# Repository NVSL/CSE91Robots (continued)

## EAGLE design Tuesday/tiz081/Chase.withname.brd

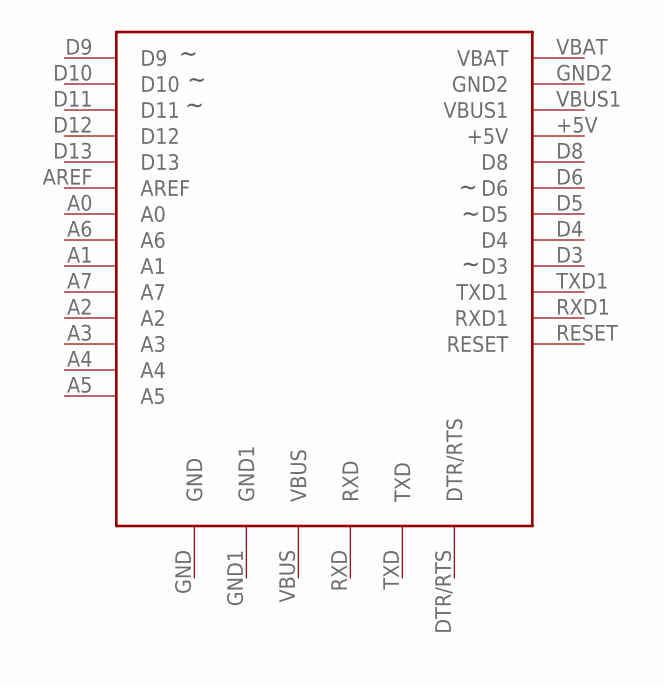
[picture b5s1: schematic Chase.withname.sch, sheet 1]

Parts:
U1_0_BRAIN: ADAFRUIT-PRO-TRINKET-5V-BOB; ADAFRUIT-PRO-TRINKET-5V

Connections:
+5V_0_BRAIN: U1_0_BRAIN.+5V; also elsewhere on the board
A0_0_BRAIN: U1_0_BRAIN.A0; also elsewhere on the board
A1_0_BRAIN: U1_0_BRAIN.A1; also elsewhere on the board
A2_0_BRAIN: U1_0_BRAIN.A2; also elsewhere on the board
A3_0_BRAIN: U1_0_BRAIN.A3; also elsewhere on the board
A4_0_BRAIN: U1_0_BRAIN.A4
A5_0_BRAIN: U1_0_BRAIN.A5
A6_0_BRAIN: U1_0_BRAIN.A6
A7_0_BRAIN: U1_0_BRAIN.A7
AREF_0_BRAIN: U1_0_BRAIN.AREF
D3_0_BRAIN: U1_0_BRAIN.D3; also elsewhere on the board
D4_0_BRAIN: U1_0_BRAIN.D4; also elsewhere on the board
D5_0_BRAIN: U1_0_BRAIN.D5; also elsewhere on the board
D6_0_BRAIN: U1_0_BRAIN.D6; also elsewhere on the board
D8_0_BRAIN: U1_0_BRAIN.D8; also elsewhere on the board
D9_0_BRAIN: U1_0_BRAIN.D9; also elsewhere on the board
D10_0_BRAIN: U1_0_BRAIN.D10; also elsewhere on the board
D11_0_BRAIN: U1_0_BRAIN.D11; also elsewhere on the board
D12_0_BRAIN: U1_0_BRAIN.D12; also elsewhere on the board
D13_0_BRAIN: U1_0_BRAIN.D13; also elsewhere on the board
DTR/RTS_0_BRAIN: U1_0_BRAIN.DTR/RTS
GND2_0_BRAIN: U1_0_BRAIN.GND, U1_0_BRAIN.GND1, U1_0_BRAIN.GND2; also elsewhere on the board
RESET_0_BRAIN: U1_0_BRAIN.RESET
RXD1_0_BRAIN: U1_0_BRAIN.RXD1
RXD_0_BRAIN: U1_0_BRAIN.RXD
TXD1_0_BRAIN: U1_0_BRAIN.TXD1
TXD_0_BRAIN: U1_0_BRAIN.TXD
VBUS1_0_BRAIN: U1_0_BRAIN.VBUS1
VBUS_0_BRAIN: U1_0_BRAIN.VBUS
VM_2_DRIVE: U1_0_BRAIN.VBAT; also elsewhere on the board

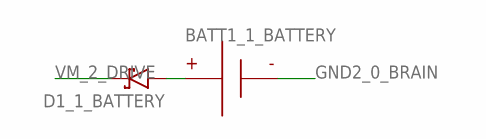
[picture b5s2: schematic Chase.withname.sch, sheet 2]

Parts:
BATT1_1_BATTERY: BATTERY-9V-VERTICAL; BATTERY_9V_KEYSTONE_968
D1_1_BATTERY: RESOLVED-DIODE-SCHOTTKY_TH-DO-41-AND-DO-204AL; DIOAD1125W78L520D270_HS; MPN 1N5817

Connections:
GND2_0_BRAIN: BATT1_1_BATTERY.N; also elsewhere on the board
unnamed: BATT1_1_BATTERY.P, D1_1_BATTERY.A
VM_2_DRIVE: D1_1_BATTERY.C; also elsewhere on the board

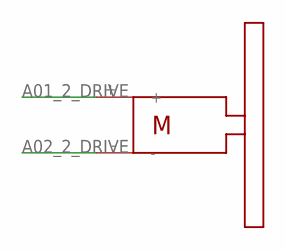
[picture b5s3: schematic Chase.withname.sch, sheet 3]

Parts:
R_2_DRIVE: SOLARBOTICS_GM2SPARKFUN_HOBBY; SPARKFUN_HOBBY_MOTOR

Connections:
A01_2_DRIVE: R_2_DRIVE.+; also elsewhere on the board
A02_2_DRIVE: R_2_DRIVE.-; also elsewhere on the board

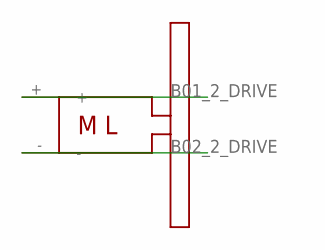
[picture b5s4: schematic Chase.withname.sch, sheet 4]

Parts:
L_2_DRIVE: SOLARBOTICS_GM2_LEFTSPARKFUN_HOBBY; SPARKFUN_HOBBY_MOTOR_LEFT

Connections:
B01_2_DRIVE: L_2_DRIVE.+; also elsewhere on the board
B02_2_DRIVE: L_2_DRIVE.-; also elsewhere on the board

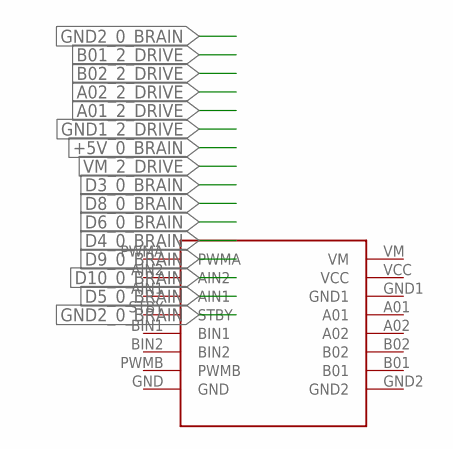
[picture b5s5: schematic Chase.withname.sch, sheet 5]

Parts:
DRVR_2_DRIVE: SPARKFUN_DUAL_MOTOR_DRIVER-BOB; SPARKFUN_DUAL_MOTOR_DRIVER

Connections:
+5V_0_BRAIN: DRVR_2_DRIVE.VCC; also elsewhere on the board
A01_2_DRIVE: DRVR_2_DRIVE.A01; also elsewhere on the board
A02_2_DRIVE: DRVR_2_DRIVE.A02; also elsewhere on the board
B01_2_DRIVE: DRVR_2_DRIVE.B01; also elsewhere on the board
B02_2_DRIVE: DRVR_2_DRIVE.B02; also elsewhere on the board
D3_0_BRAIN: DRVR_2_DRIVE.PWMA; also elsewhere on the board
D4_0_BRAIN: DRVR_2_DRIVE.STBY; also elsewhere on the board
D5_0_BRAIN: DRVR_2_DRIVE.PWMB; also elsewhere on the board
D6_0_BRAIN: DRVR_2_DRIVE.AIN1; also elsewhere on the board
D8_0_BRAIN: DRVR_2_DRIVE.AIN2; also elsewhere on the board
D9_0_BRAIN: DRVR_2_DRIVE.BIN1; also elsewhere on the board
D10_0_BRAIN: DRVR_2_DRIVE.BIN2; also elsewhere on the board
GND1_2_DRIVE: DRVR_2_DRIVE.GND1
GND2_0_BRAIN: DRVR_2_DRIVE.GND, DRVR_2_DRIVE.GND2; also elsewhere on the board
VM_2_DRIVE: DRVR_2_DRIVE.VM; also elsewhere on the board

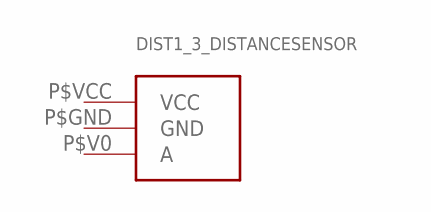
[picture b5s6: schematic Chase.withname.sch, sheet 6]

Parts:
DIST1_3_DISTANCESENSOR: ANALOG_DISTANCE_SENSOR

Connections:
+5V_0_BRAIN: DIST1_3_DISTANCESENSOR.P$VCC (VCC); also elsewhere on the board
A2_0_BRAIN: DIST1_3_DISTANCESENSOR.P$V0 (A); also elsewhere on the board
GND2_0_BRAIN: DIST1_3_DISTANCESENSOR.P$GND (GND); also elsewhere on the board

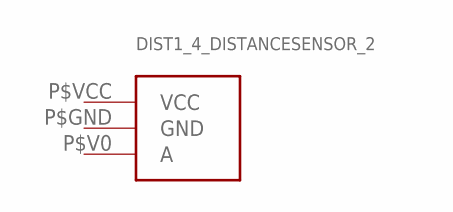
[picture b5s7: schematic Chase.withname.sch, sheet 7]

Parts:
DIST1_4_DISTANCESENSOR_2: ANALOG_DISTANCE_SENSOR

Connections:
+5V_0_BRAIN: DIST1_4_DISTANCESENSOR_2.P$VCC (VCC); also elsewhere on the board
A3_0_BRAIN: DIST1_4_DISTANCESENSOR_2.P$V0 (A); also elsewhere on the board
GND2_0_BRAIN: DIST1_4_DISTANCESENSOR_2.P$GND (GND); also elsewhere on the board

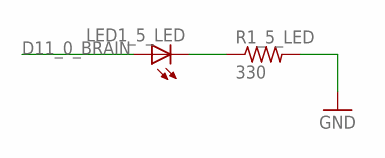
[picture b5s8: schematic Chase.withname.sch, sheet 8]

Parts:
LED1_5_LED: LED5MM
R1_5_LED: 330; RESAD770W45L370D210_HS; MPN CFR-12JB-52-330R

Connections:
D11_0_BRAIN: LED1_5_LED.A; also elsewhere on the board
GND2_0_BRAIN: R1_5_LED.2; also elsewhere on the board
unnamed: LED1_5_LED.K (C), R1_5_LED.1

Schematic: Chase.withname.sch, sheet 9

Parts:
LED1_6_LED_2: LED5MM
R1_6_LED_2: 330; RESAD770W45L370D210_HS; MPN CFR-12JB-52-330R

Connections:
D12_0_BRAIN: LED1_6_LED_2.A; also elsewhere on the board
GND2_0_BRAIN: R1_6_LED_2.2; also elsewhere on the board
unnamed: LED1_6_LED_2.K (C), R1_6_LED_2.1

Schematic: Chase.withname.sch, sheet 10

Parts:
LED1_7_LED_3: LED5MM
R1_7_LED_3: 330; RESAD770W45L370D210_HS; MPN CFR-12JB-52-330R

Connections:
D13_0_BRAIN: LED1_7_LED_3.A; also elsewhere on the board
GND2_0_BRAIN: R1_7_LED_3.2; also elsewhere on the board
unnamed: LED1_7_LED_3.K (C), R1_7_LED_3.1

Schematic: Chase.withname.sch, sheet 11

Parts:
U1_8_CASTER: CASTERADAFRUIT-3/4IN; ADAFRUIT-3/4IN-CASTER

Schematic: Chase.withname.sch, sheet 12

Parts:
B1_9_BUTTON: BUTTON-TACTILE-ROUND; BUTTON-TACTILE-ROUND-ADAFRUIT1009

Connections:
A0_0_BRAIN: B1_9_BUTTON.P; also elsewhere on the board
GND2_0_BRAIN: B1_9_BUTTON.S; also elsewhere on the board

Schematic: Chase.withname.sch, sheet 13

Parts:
U$2_10_BUMP: BUMP_SWITCH-MEDIUM-RIGHT; BUMP_SWITCH_OMRON_D2FLA1

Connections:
A1_0_BRAIN: U$2_10_BUMP.A; also elsewhere on the board
GND2_0_BRAIN: U$2_10_BUMP.B; also elsewhere on the board

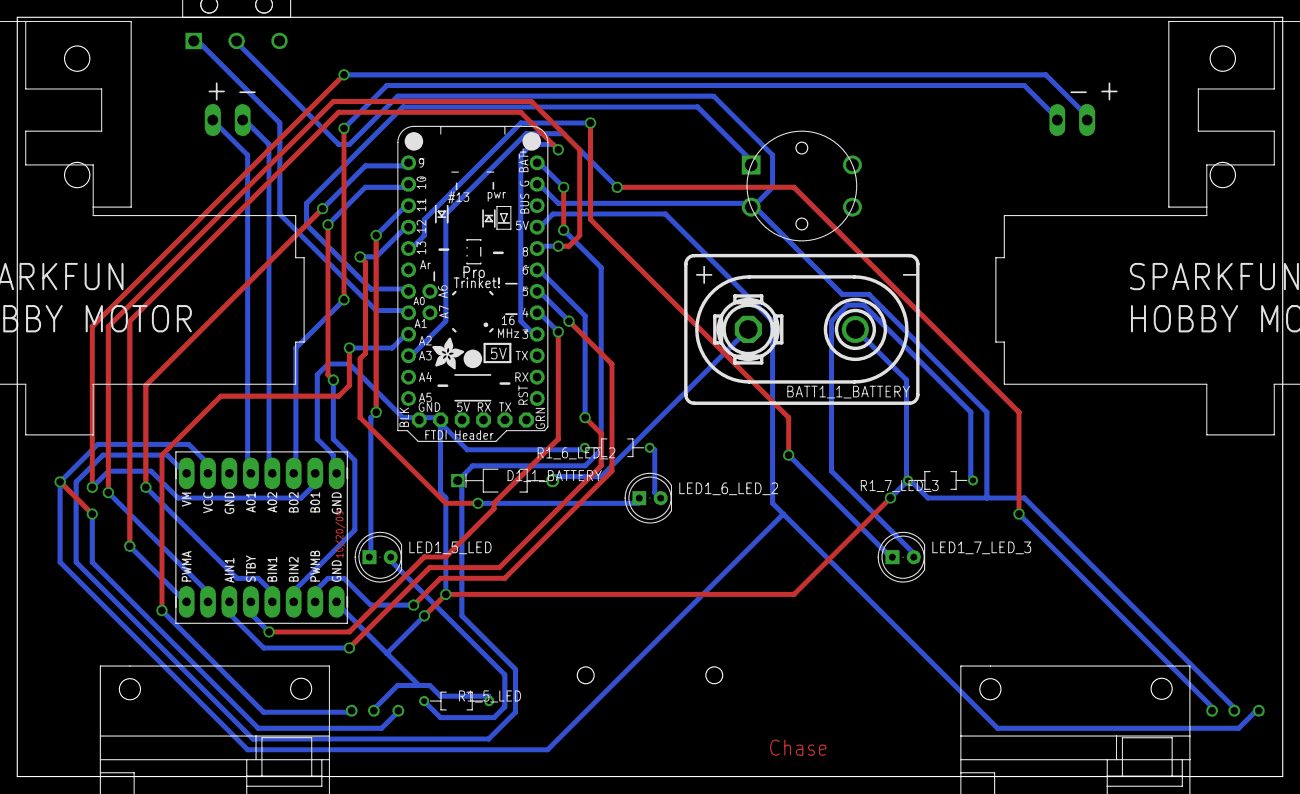
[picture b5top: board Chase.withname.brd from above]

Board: 2 copper layers, 150.0 x 90.0 mm, 17 parts (0 on the bottom side), 25 nets.

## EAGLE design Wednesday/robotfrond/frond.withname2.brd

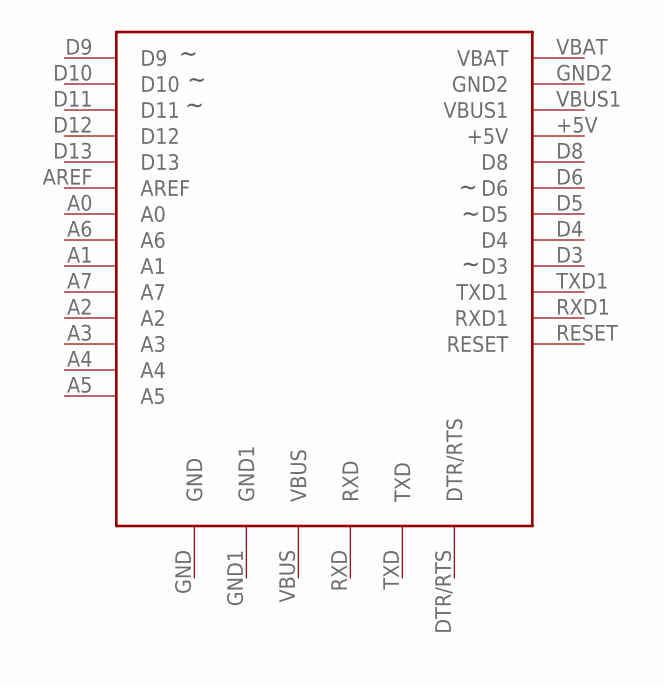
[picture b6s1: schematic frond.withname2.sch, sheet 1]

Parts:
U1_0_BRAIN: ADAFRUIT-PRO-TRINKET-5V-BOB; ADAFRUIT-PRO-TRINKET-5V

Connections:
+5V_0_BRAIN: U1_0_BRAIN.+5V; also elsewhere on the board
A0_0_BRAIN: U1_0_BRAIN.A0
A1_0_BRAIN: U1_0_BRAIN.A1
A2_0_BRAIN: U1_0_BRAIN.A2
A3_0_BRAIN: U1_0_BRAIN.A3
A4_0_BRAIN: U1_0_BRAIN.A4; also elsewhere on the board
A5_0_BRAIN: U1_0_BRAIN.A5; also elsewhere on the board
A6_0_BRAIN: U1_0_BRAIN.A6
A7_0_BRAIN: U1_0_BRAIN.A7
AREF_0_BRAIN: U1_0_BRAIN.AREF
D3_0_BRAIN: U1_0_BRAIN.D3; also elsewhere on the board
D4_0_BRAIN: U1_0_BRAIN.D4; also elsewhere on the board
D5_0_BRAIN: U1_0_BRAIN.D5; also elsewhere on the board
D6_0_BRAIN: U1_0_BRAIN.D6; also elsewhere on the board
D8_0_BRAIN: U1_0_BRAIN.D8; also elsewhere on the board
D9_0_BRAIN: U1_0_BRAIN.D9; also elsewhere on the board
D10_0_BRAIN: U1_0_BRAIN.D10; also elsewhere on the board
D11_0_BRAIN: U1_0_BRAIN.D11; also elsewhere on the board
D12_0_BRAIN: U1_0_BRAIN.D12; also elsewhere on the board
D13_0_BRAIN: U1_0_BRAIN.D13; also elsewhere on the board
DTR/RTS_0_BRAIN: U1_0_BRAIN.DTR/RTS
GND2_0_BRAIN: U1_0_BRAIN.GND, U1_0_BRAIN.GND1, U1_0_BRAIN.GND2; also elsewhere on the board
RESET_0_BRAIN: U1_0_BRAIN.RESET
RXD1_0_BRAIN: U1_0_BRAIN.RXD1
RXD_0_BRAIN: U1_0_BRAIN.RXD
TXD1_0_BRAIN: U1_0_BRAIN.TXD1
TXD_0_BRAIN: U1_0_BRAIN.TXD
VBUS1_0_BRAIN: U1_0_BRAIN.VBUS1
VBUS_0_BRAIN: U1_0_BRAIN.VBUS
VM_8_DRIVE: U1_0_BRAIN.VBAT; also elsewhere on the board

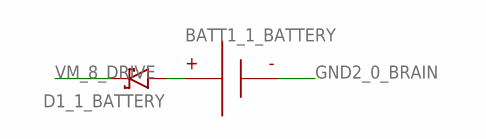
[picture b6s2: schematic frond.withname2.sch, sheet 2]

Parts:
BATT1_1_BATTERY: BATTERY-9V-VERTICAL; BATTERY_9V_KEYSTONE_968
D1_1_BATTERY: RESOLVED-DIODE-SCHOTTKY_TH-DO-41-AND-DO-204AL; DIOAD1125W78L520D270_HS; MPN 1N5817

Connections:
GND2_0_BRAIN: BATT1_1_BATTERY.N; also elsewhere on the board
unnamed: BATT1_1_BATTERY.P, D1_1_BATTERY.A
VM_8_DRIVE: D1_1_BATTERY.C; also elsewhere on the board

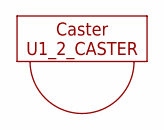
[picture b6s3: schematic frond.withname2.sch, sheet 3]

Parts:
U1_2_CASTER: CASTERADAFRUIT-3/4IN; ADAFRUIT-3/4IN-CASTER

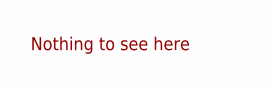
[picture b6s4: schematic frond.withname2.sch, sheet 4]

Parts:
U1_3_PENHOLDER: PENHOLDER

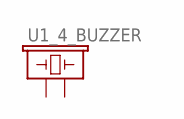
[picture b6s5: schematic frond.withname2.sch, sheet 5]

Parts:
U1_4_BUZZER: BUZZERPTH; BUZZER-12MM

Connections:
D4_0_BRAIN: U1_4_BUZZER.+ (1); also elsewhere on the board
GND2_0_BRAIN: U1_4_BUZZER.- (2); also elsewhere on the board

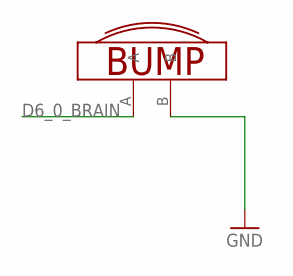
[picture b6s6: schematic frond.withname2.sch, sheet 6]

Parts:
U$2_5_BUMP: BUMP_SWITCH-MEDIUM-RIGHT; BUMP_SWITCH_OMRON_D2FLA1

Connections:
D6_0_BRAIN: U$2_5_BUMP.A; also elsewhere on the board
GND2_0_BRAIN: U$2_5_BUMP.B; also elsewhere on the board

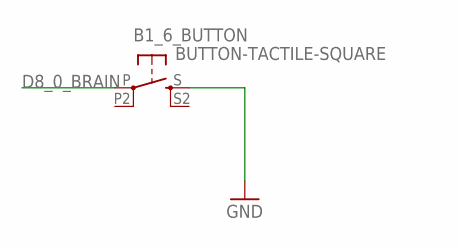
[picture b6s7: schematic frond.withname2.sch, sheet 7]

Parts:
B1_6_BUTTON: BUTTON-TACTILE-SQUARE; BUTTON-TACTILE-SQUARE-ADAFRUIT1010

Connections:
D8_0_BRAIN: B1_6_BUTTON.P; also elsewhere on the board
GND2_0_BRAIN: B1_6_BUTTON.S; also elsewhere on the board

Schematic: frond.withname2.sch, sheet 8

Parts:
U1_7_DISPLAY_2: ADAFRUIT-1.2IN-8X8-LED-BACKPACK-BOB; ADAFRUIT-1.2IN-8X8-LED-BACKPACK

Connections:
+5V_0_BRAIN: U1_7_DISPLAY_2.VDD; also elsewhere on the board
A4_0_BRAIN: U1_7_DISPLAY_2.SDA; also elsewhere on the board
A5_0_BRAIN: U1_7_DISPLAY_2.SCL; also elsewhere on the board
GND2_0_BRAIN: U1_7_DISPLAY_2.GND; also elsewhere on the board

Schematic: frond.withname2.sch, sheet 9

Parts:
R_8_DRIVE: SOLARBOTICS_GM2; SOLARBOTICS_G2

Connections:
A01_8_DRIVE: R_8_DRIVE.+; also elsewhere on the board
A02_8_DRIVE: R_8_DRIVE.-; also elsewhere on the board

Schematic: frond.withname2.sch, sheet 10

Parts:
L_8_DRIVE: SOLARBOTICS_GM2_LEFT; SOLARBOTICS_G2_LEFT

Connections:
B01_8_DRIVE: L_8_DRIVE.+; also elsewhere on the board
B02_8_DRIVE: L_8_DRIVE.-; also elsewhere on the board

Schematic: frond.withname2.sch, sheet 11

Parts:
DRVR_8_DRIVE: SPARKFUN_DUAL_MOTOR_DRIVER-BOB; SPARKFUN_DUAL_MOTOR_DRIVER

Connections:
+5V_0_BRAIN: DRVR_8_DRIVE.VCC; also elsewhere on the board
A01_8_DRIVE: DRVR_8_DRIVE.A01; also elsewhere on the board
A02_8_DRIVE: DRVR_8_DRIVE.A02; also elsewhere on the board
B01_8_DRIVE: DRVR_8_DRIVE.B01; also elsewhere on the board
B02_8_DRIVE: DRVR_8_DRIVE.B02; also elsewhere on the board
D3_0_BRAIN: DRVR_8_DRIVE.PWMA; also elsewhere on the board
D5_0_BRAIN: DRVR_8_DRIVE.PWMB; also elsewhere on the board
D9_0_BRAIN: DRVR_8_DRIVE.STBY; also elsewhere on the board
D10_0_BRAIN: DRVR_8_DRIVE.AIN1; also elsewhere on the board
D11_0_BRAIN: DRVR_8_DRIVE.AIN2; also elsewhere on the board
D12_0_BRAIN: DRVR_8_DRIVE.BIN1; also elsewhere on the board
D13_0_BRAIN: DRVR_8_DRIVE.BIN2; also elsewhere on the board
GND1_8_DRIVE: DRVR_8_DRIVE.GND1
GND2_0_BRAIN: DRVR_8_DRIVE.GND, DRVR_8_DRIVE.GND2; also elsewhere on the board
VM_8_DRIVE: DRVR_8_DRIVE.VM; also elsewhere on the board

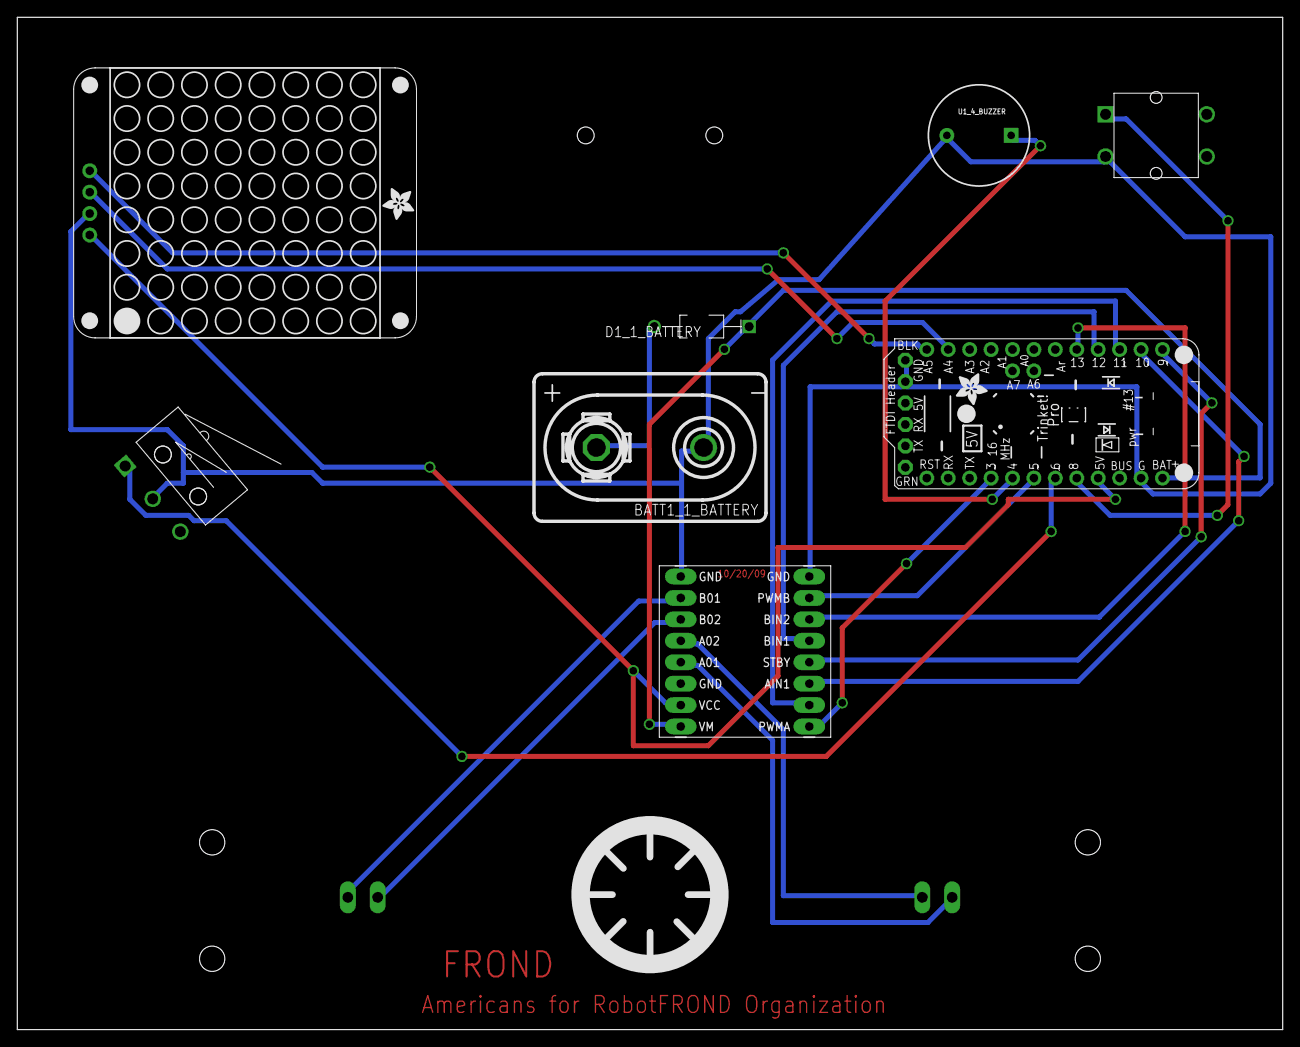
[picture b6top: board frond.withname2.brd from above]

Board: 2 copper layers, 150.0 x 120.0 mm, 12 parts (0 on the bottom side), 20 nets.

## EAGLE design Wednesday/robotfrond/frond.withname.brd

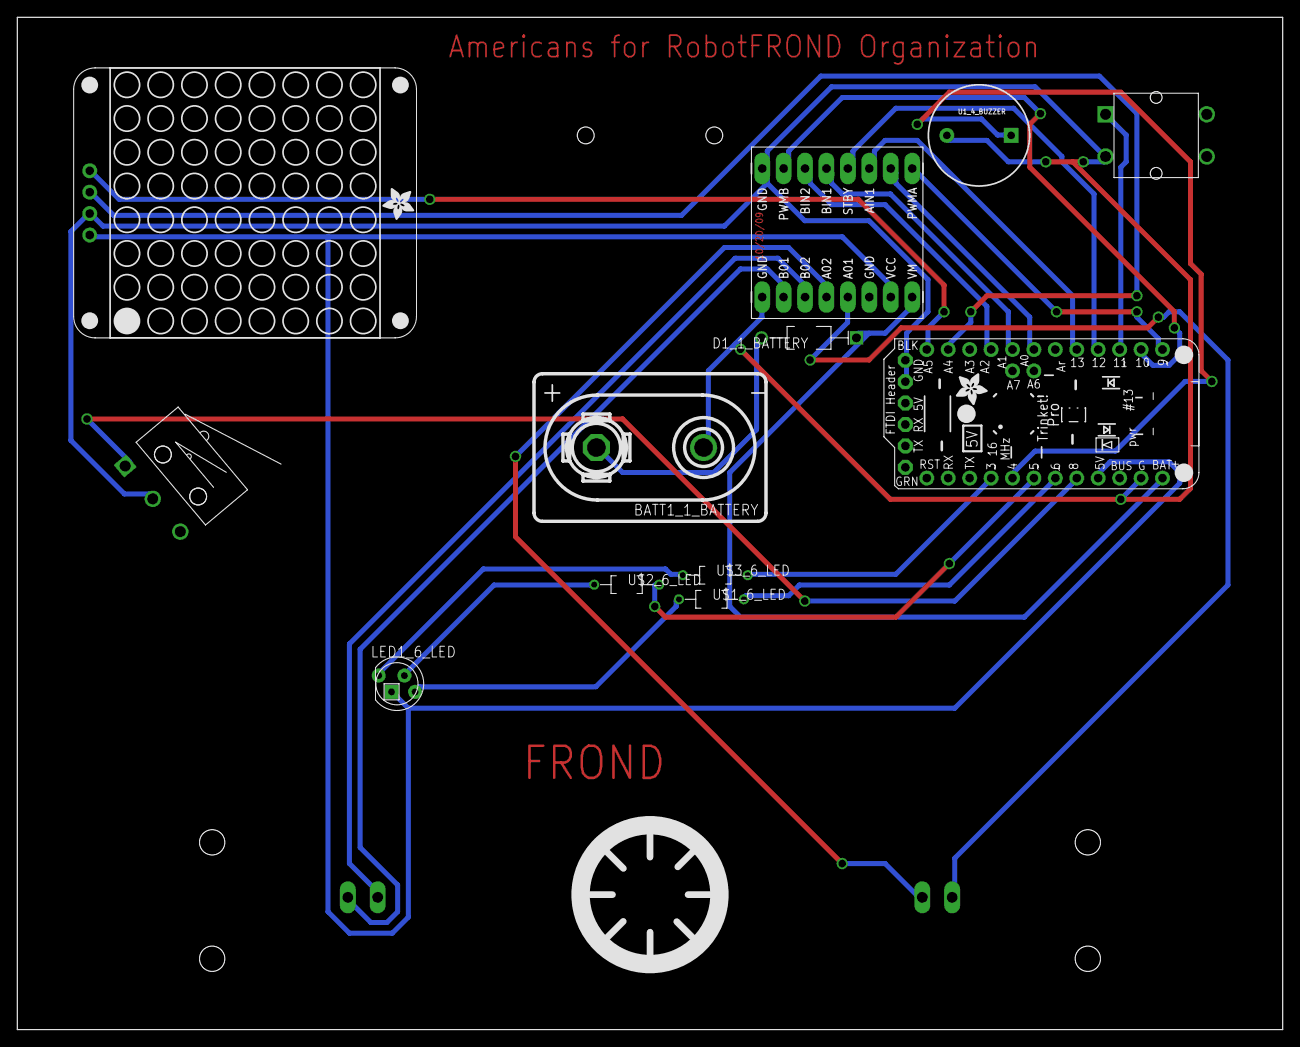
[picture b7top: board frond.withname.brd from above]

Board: 2 copper layers, 150.0 x 120.0 mm, 16 parts (0 on the bottom side), 26 nets.

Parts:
B1_7_BUTTON: BUTTON-TACTILE-SQUARE; BUTTON-TACTILE-SQUARE-ADAFRUIT1010
BATT1_1_BATTERY: BATTERY-9V-VERTICAL; BATTERY_9V_KEYSTONE_968
D1_1_BATTERY: DIOAD1125W78L520D270_HS
DRVR_9_DRIVE: SPARKFUN_DUAL_MOTOR_DRIVER-BOB; SPARKFUN_DUAL_MOTOR_DRIVER
LED1_6_LED: RGBLED_CA-5MM; LED5MMRGB
L_9_DRIVE: SOLARBOTICS_GM2_LEFT; SOLARBOTICS_G2_LEFT
R_9_DRIVE: SOLARBOTICS_GM2; SOLARBOTICS_G2
U1_0_BRAIN: ADAFRUIT-PRO-TRINKET-5V
U1_2_CASTER: ADAFRUIT-3/4IN-CASTER
U1_3_PENHOLDER: PENHOLDER
U1_4_BUZZER: BUZZER-12MM
U1_8_DISPLAY_2: ADAFRUIT-1.2IN-8X8-LED-BACKPACK
U$1_6_LED, U$2_6_LED: 100; RESAD770W45L370D210_HS
U$2_5_BUMP: BUMP_SWITCH-MEDIUM-RIGHT; BUMP_SWITCH_OMRON_D2FLA1
U$3_6_LED: 150; RESAD770W45L370D210_HS

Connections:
+5V_0_BRAIN: DRVR_9_DRIVE.VCC, LED1_6_LED.2, U1_0_BRAIN.+5V, U1_8_DISPLAY_2.VDD
A0_0_BRAIN: DRVR_9_DRIVE.AIN2, U1_0_BRAIN.A0
A1_0_BRAIN: DRVR_9_DRIVE.BIN1, U1_0_BRAIN.A1
A01_9_DRIVE: DRVR_9_DRIVE.A01, R_9_DRIVE.+
A2_0_BRAIN: DRVR_9_DRIVE.BIN2, U1_0_BRAIN.A2
A02_9_DRIVE: DRVR_9_DRIVE.A02, R_9_DRIVE.-
A4_0_BRAIN: U1_0_BRAIN.A4, U1_8_DISPLAY_2.SDA
A5_0_BRAIN: U1_0_BRAIN.A5, U1_8_DISPLAY_2.SCL
B01_9_DRIVE: DRVR_9_DRIVE.B01, L_9_DRIVE.+
B02_9_DRIVE: DRVR_9_DRIVE.B02, L_9_DRIVE.-
D3_0_BRAIN: U1_0_BRAIN.D3, U$3_6_LED.2
D4_0_BRAIN: U1_0_BRAIN.D4, U1_4_BUZZER.+
D5_0_BRAIN: U1_0_BRAIN.D5, U$2_6_LED.2
D6_0_BRAIN: U1_0_BRAIN.D6, U$1_6_LED.2
D8_0_BRAIN: U1_0_BRAIN.D8, U$2_5_BUMP.A
D9_0_BRAIN: DRVR_9_DRIVE.PWMA, U1_0_BRAIN.D9
D10_0_BRAIN: DRVR_9_DRIVE.PWMB, U1_0_BRAIN.D10
D11_0_BRAIN: B1_7_BUTTON.P, U1_0_BRAIN.D11
D12_0_BRAIN: DRVR_9_DRIVE.STBY, U1_0_BRAIN.D12
D13_0_BRAIN: DRVR_9_DRIVE.AIN1, U1_0_BRAIN.D13
GND2_0_BRAIN: B1_7_BUTTON.S, BATT1_1_BATTERY.N, DRVR_9_DRIVE.GND, DRVR_9_DRIVE.GND2, U1_0_BRAIN.GND, U1_0_BRAIN.GND1, U1_0_BRAIN.GND2, U1_4_BUZZER.-, U1_8_DISPLAY_2.GND, U$2_5_BUMP.B
unnamed: BATT1_1_BATTERY.P, D1_1_BATTERY.A
unnamed: LED1_6_LED.4, U$1_6_LED.1
unnamed: LED1_6_LED.3, U$2_6_LED.1
unnamed: LED1_6_LED.1, U$3_6_LED.1
VM_9_DRIVE: D1_1_BATTERY.C, DRVR_9_DRIVE.VM, U1_0_BRAIN.VBAT

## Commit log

2015-11-06 Made a directories in designs for students gspecs
2015-11-06 Added all students gspecs and makefiles to designs
2015-11-06 Removed overlapping pins on Chase
2015-11-07 fixed gspec for more space enough for motor driver
2015-11-07 Corrected Chase's gspec and routed board
2015-11-07 Renamed group njw's robot to Wall-E (requested by group members)
2015-11-07 Fixed dimension issues with gspec, added updated Makefile
2015-11-09 Accidentally committed every single half baked modification in my working copy
2015-11-09 bling
2015-11-09 Wall-E
2015-11-10 changed the name
2015-11-10 Bad makefile
2015-11-10 bost fronds forovor
2015-11-10 woll smoth approves of his new robot frond
2015-11-10 Forgot to delete rgb led from gspec
2015-11-10 Expanded drills because we have run out of 0.8mm
2015-11-10 Gave it a name
2015-11-10 Added robotfrond brd and sch
2015-11-10 Bigger text
2015-11-10 JAK drill sizes changed
2015-11-10 Test code
2015-11-10 Renamed dlj to BashKetchum
2015-11-10 Renamed Joanna to PessimistPrime
2015-11-10 read me
2015-11-11 Added routed PessimistPrime files
2015-11-11 Added BashKetchum routed board with name
2015-11-12 Wall-E is good to go!
2015-11-12 Monsterbot
2015-11-12 Invalid name
2015-11-12 Invalid placement of bump sensors
2015-11-12 Sun, with only 26 vias
2015-11-13 Readme
2015-11-13 Added Chase's auto generated code
2015-11-13 didn't need those
2015-11-14 HotlineBling test code
2015-11-14 Jak works
2015-11-15 Added h files for several CSE91 Robots
2015-11-16 BashKetchum test
2015-11-16 don’t need
2015-11-16 Changed name
2015-11-16 Folder name
2015-11-16 Chase_test ino
